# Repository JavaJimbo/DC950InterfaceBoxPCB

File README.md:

# DC950InterfaceBoxPCB
Interface box released for production in December 2017

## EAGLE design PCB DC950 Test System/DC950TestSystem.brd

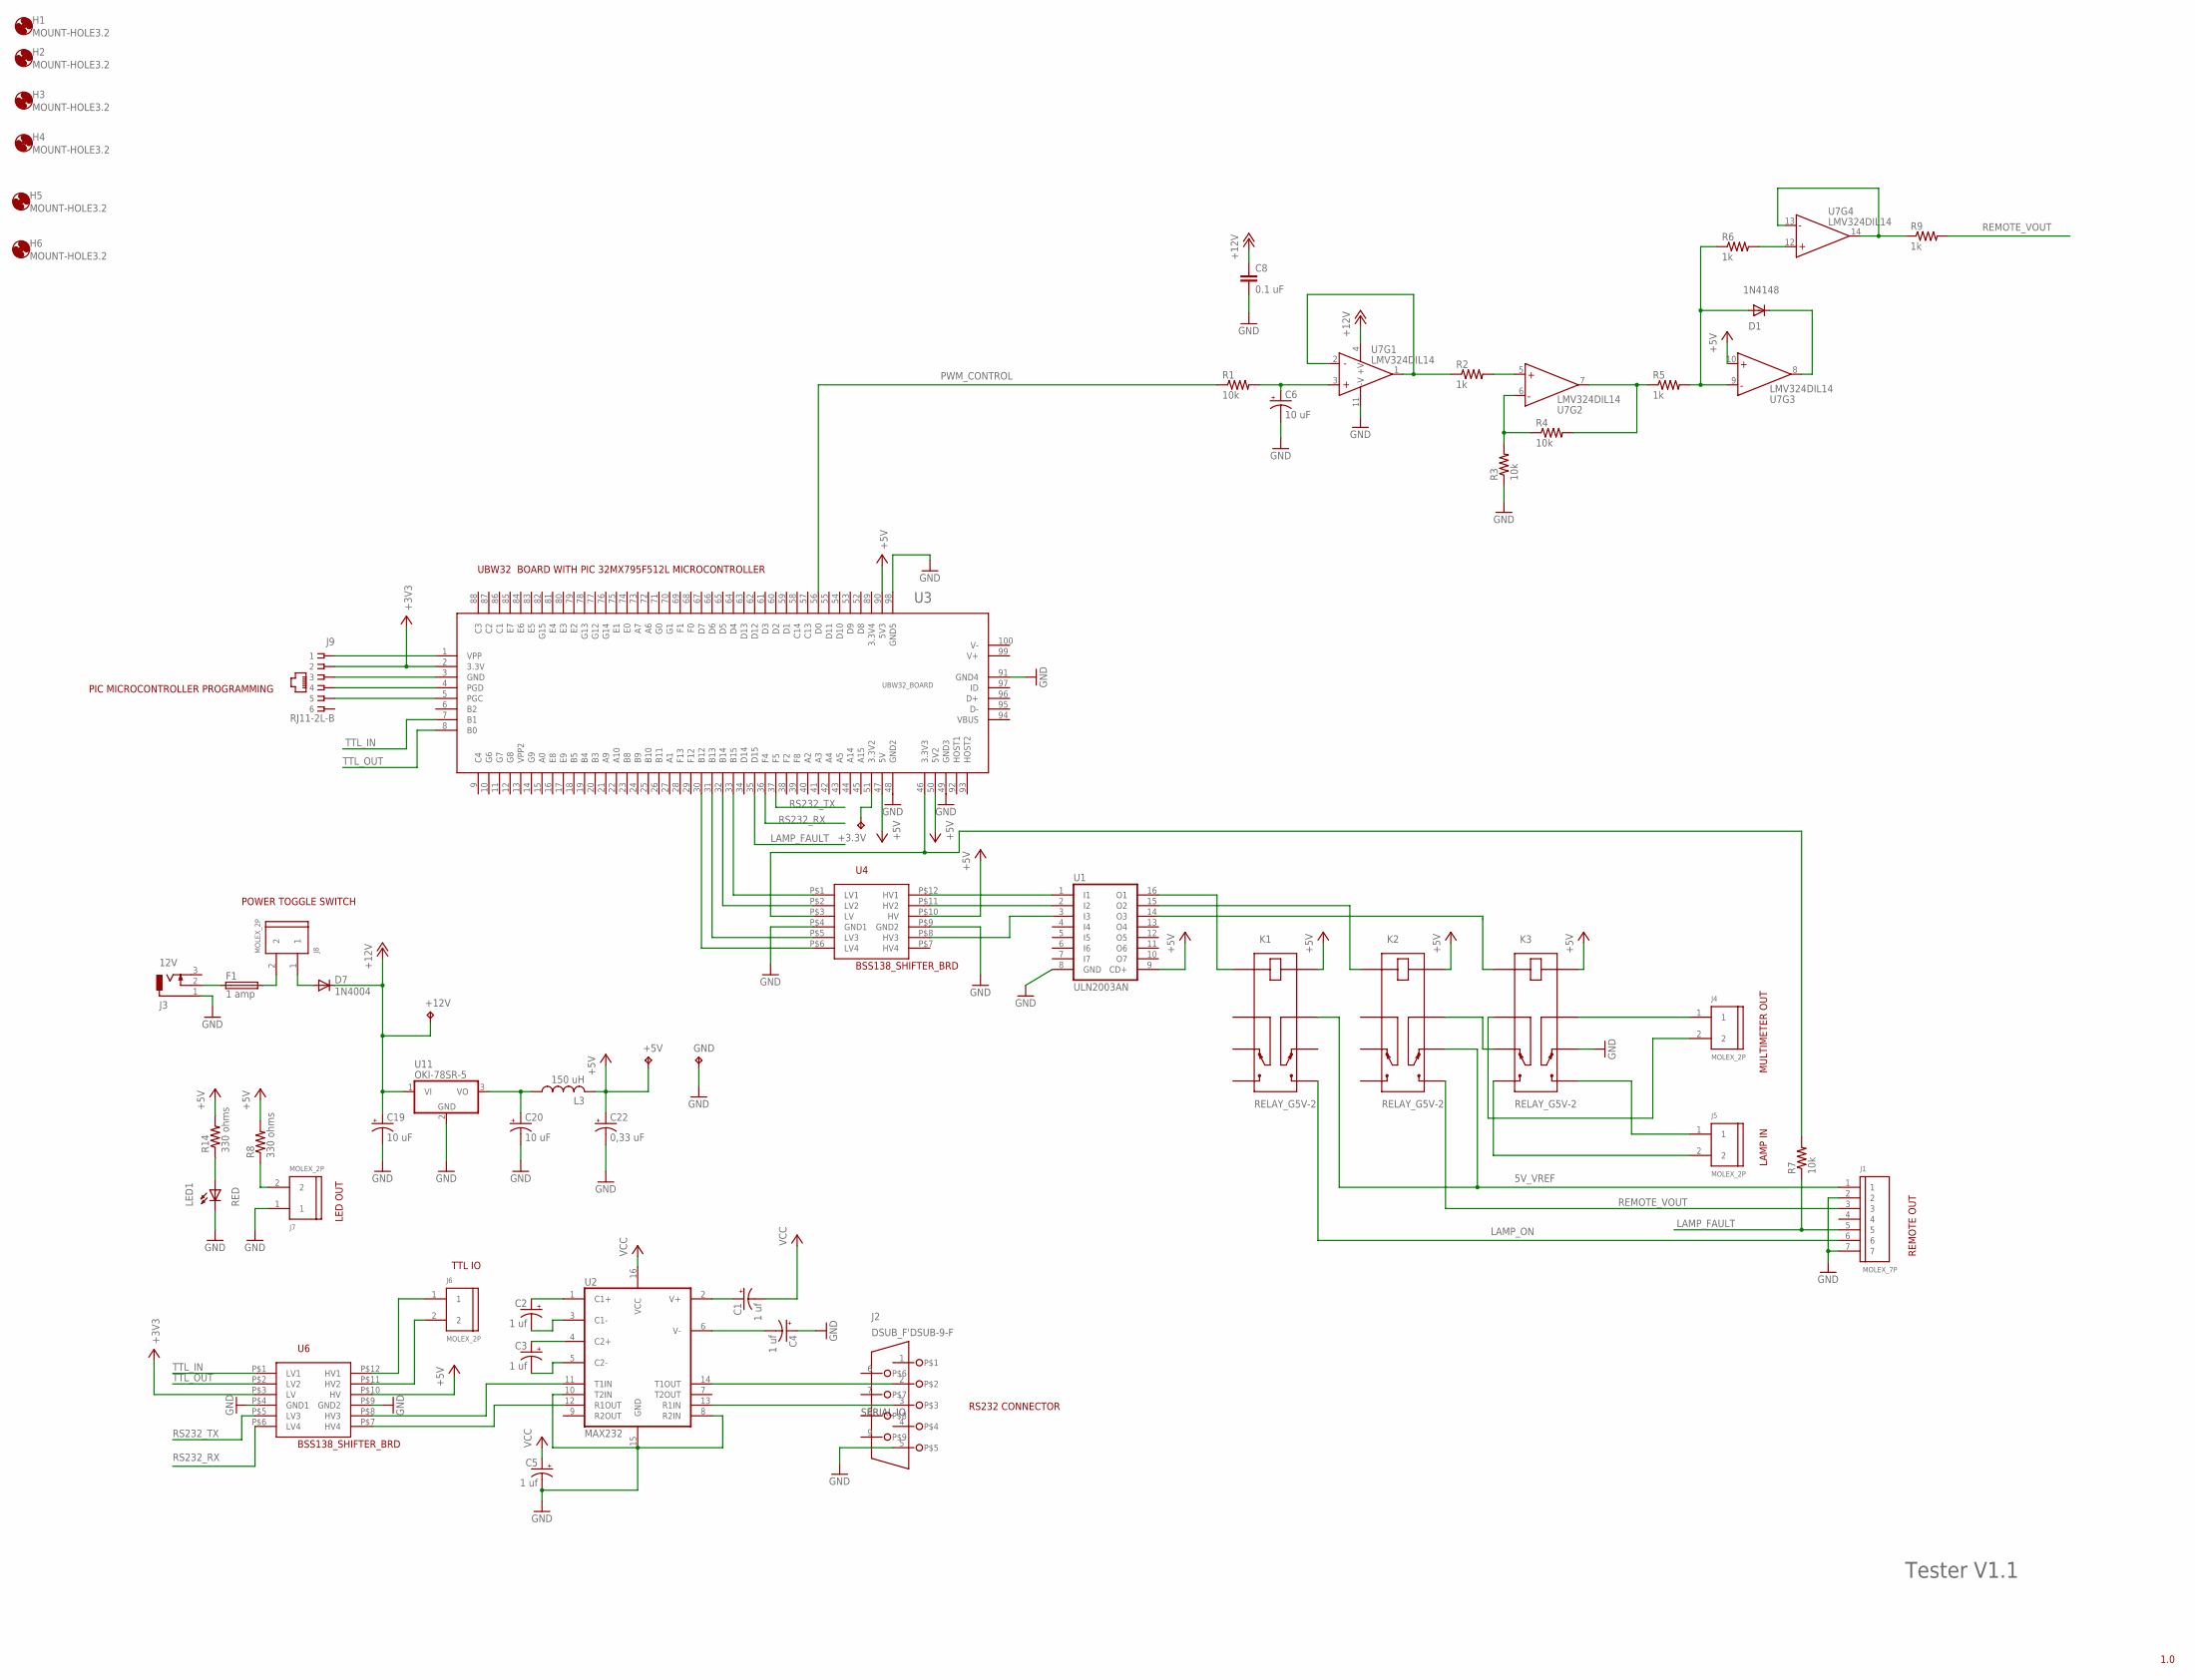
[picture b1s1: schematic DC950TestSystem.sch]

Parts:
+3.3V, +5V, +12V: TP; TESTPAD
C1, C2, C3, C4, C5: 1 uf; E2-5
C6, C19, C20: 10 uF; E2-5
C8: 0.1 uF; C5B2.5
C22: 0,33 uF; E2-5
D1: 1N4148; DO35-10
D7: 1N4004; DO41-10
F1: 1 amp; SH22,5
GND: TP; TESTPAD
H1, H2, H3, H4, H5, H6: MOUNT-HOLE3.2; 3,2
J1: MOLEX_7P
J2: DSUB_F'DSUB-9-F; H5M09RA
J3: 12V; DCJ0303
J4, J5, J6, J7, J8: MOLEX_2P
J9: RJ11-2L-B; RJ11-NO_SHIELD
K1, K2, K3: RELAY_G5V-2
L3: 150 uH; 0204/7
LED1: RED; LED5MM
R1, R3, R4, R7: 10k; 1/4_WATT
R2, R5, R6, R9: 1k; 1/4_WATT
R8, R14: 330 ohms; 0207/10
U1: ULN2003AN; DIL16
U2: MAX232; DIL16
U3: UBW32_BOARD; UBW32
U4, U6: BSS138_SHIFTER_BRD
U7: LMV324DIL14; DIL14
U11: OKI-78SR-5; TO220V

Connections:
3.3V4: U3.89 (3.3V4)
5V_VREF: J1.1, K1.13, K2.11
+3V3: J9.2, U3.2 (3.3V), U6.P$3 (LV)
+5V: +5V.P$1, C22.+, K1.16, K2.16, K3.16, L3.2, R8.2, R14.2, U1.9 (CD+), U3.47 (5V), U3.50 (5V2), U3.90 (5V3), U4.P$10 (HV), U6.P$10 (HV), U7.10 (+IN)
+12V: +12V.P$1, C8.1, C19.+, D7.C, U7.4 (+V), U11.1 (VI)
GND: C4.+, C5.-, C6.-, C8.2, C19.-, C20.-, C22.-, GND.P$1, J1.2, J1.7, J2.5, J3.1, J7.1, K3.11, LED1.K (C), R3.1, U1.8 (GND), U2.8 (R2IN), U2.10 (T2IN), U2.15 (GND), U3.48 (GND2), U3.49 (GND3), U3.91 (GND4), U3.98 (GND5), U4.P$4 (GND1), U4.P$9 (GND2), U6.P$4 (GND1), U6.P$9 (GND2), U7.11 (-V), U11.2 (GND)
LAMP_FAULT: J1.5, R7.1, U3.35 (D15)
LAMP_ON: J1.6, K1.9
unnamed: F1.1, J3.2
unnamed: J9.3, U3.3 (GND)
unnamed: F1.2, J8.2
unnamed: U2.12 (R1OUT), U6.P$7 (HV4)
unnamed: U2.11 (T1IN), U6.P$8 (HV3)
unnamed: J9.1, U3.1 (VPP)
unnamed: J6.1, U6.P$12 (HV1)
unnamed: J9.4, U3.4 (PGD)
unnamed: J9.5, U3.5 (PGC)
unnamed: R2.1, U7.1 (OUT), U7.2 (-IN)
unnamed: C6.+, R1.2, U7.3 (+IN)
unnamed: R3.2, R4.1, U7.6 (-IN)
unnamed: R4.2, R5.1, U7.7 (OUT)
unnamed: J6.2, U6.P$11 (HV2)
unnamed: R2.2, U7.5 (+IN)
unnamed: D1.A, R5.2, R6.1, U7.9 (-IN)
unnamed: D1.C, U7.8 (OUT)
unnamed: LED1.A, R14.1
unnamed: J2.2, U2.14 (T1OUT)
unnamed: J2.3, U2.13 (R1IN)
unnamed: R6.2, U7.12 (+IN)
unnamed: R7.2, U3.46 (3.3V3), U4.P$3 (LV)
unnamed: C2.+, U2.1 (C1+)
unnamed: C2.-, U2.3 (C1-)
unnamed: C3.+, U2.4 (C2+)
unnamed: C3.-, U2.5 (C2-)
unnamed: C1.+, U2.2 (V+)
unnamed: C4.-, U2.6 (V-)
unnamed: U3.33 (B15), U4.P$1 (LV1)
unnamed: U3.32 (B14), U4.P$2 (LV2)
unnamed: U3.31 (B13), U4.P$5 (LV3)
unnamed: U3.30 (B12), U4.P$6 (LV4)
unnamed: +3.3V.P$1, U3.51 (3.3V2)
unnamed: U1.1 (I1), U4.P$12 (HV1)
unnamed: U1.2 (I2), U4.P$11 (HV2)
unnamed: U1.3 (I3), U4.P$8 (HV3)
unnamed: J7.2, R8.1
unnamed: K1.1, U1.16 (O1)
unnamed: K2.1, U1.15 (O2)
unnamed: K3.1, U1.14 (O3)
unnamed: D7.A, J8.1
unnamed: C20.+, L3.1, U11.3 (VO)
unnamed: J4.1, K3.13
unnamed: J4.2, K3.4
unnamed: J5.1, K3.9
unnamed: J5.2, K3.8
unnamed: K2.13, K3.6
unnamed: R9.1, U7.13 (-IN), U7.14 (OUT)
PWM_CONTROL: R1.1, U3.56 (D0)
REMOTE_VOUT: J1.3, K2.9, R9.2
RS232_RX: U3.36 (F4), U6.P$6 (LV4)
RS232_TX: U3.37 (F5), U6.P$5 (LV3)
TTL_IN: U3.7 (B1), U6.P$1 (LV1)
TTL_OUT: U3.8 (B0), U6.P$2 (LV2)
V+: U3.99 (V+)
V-: U3.100 (V-)
VBUS: U3.94 (VBUS)
VCC: C1.-, C5.+, U2.16 (VCC)

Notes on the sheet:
SERIAL IO
1.0
Tester V1.1
MULTIMETER OUT
LAMP IN
REMOTE OUT
LED OUT
TTL IO
POWER TOGGLE SWITCH
RS232 CONNECTOR
PIC MICROCONTROLLER PROGRAMMING
UBW32 BOARD WITH PIC 32MX795F512L MICROCONTROLLER

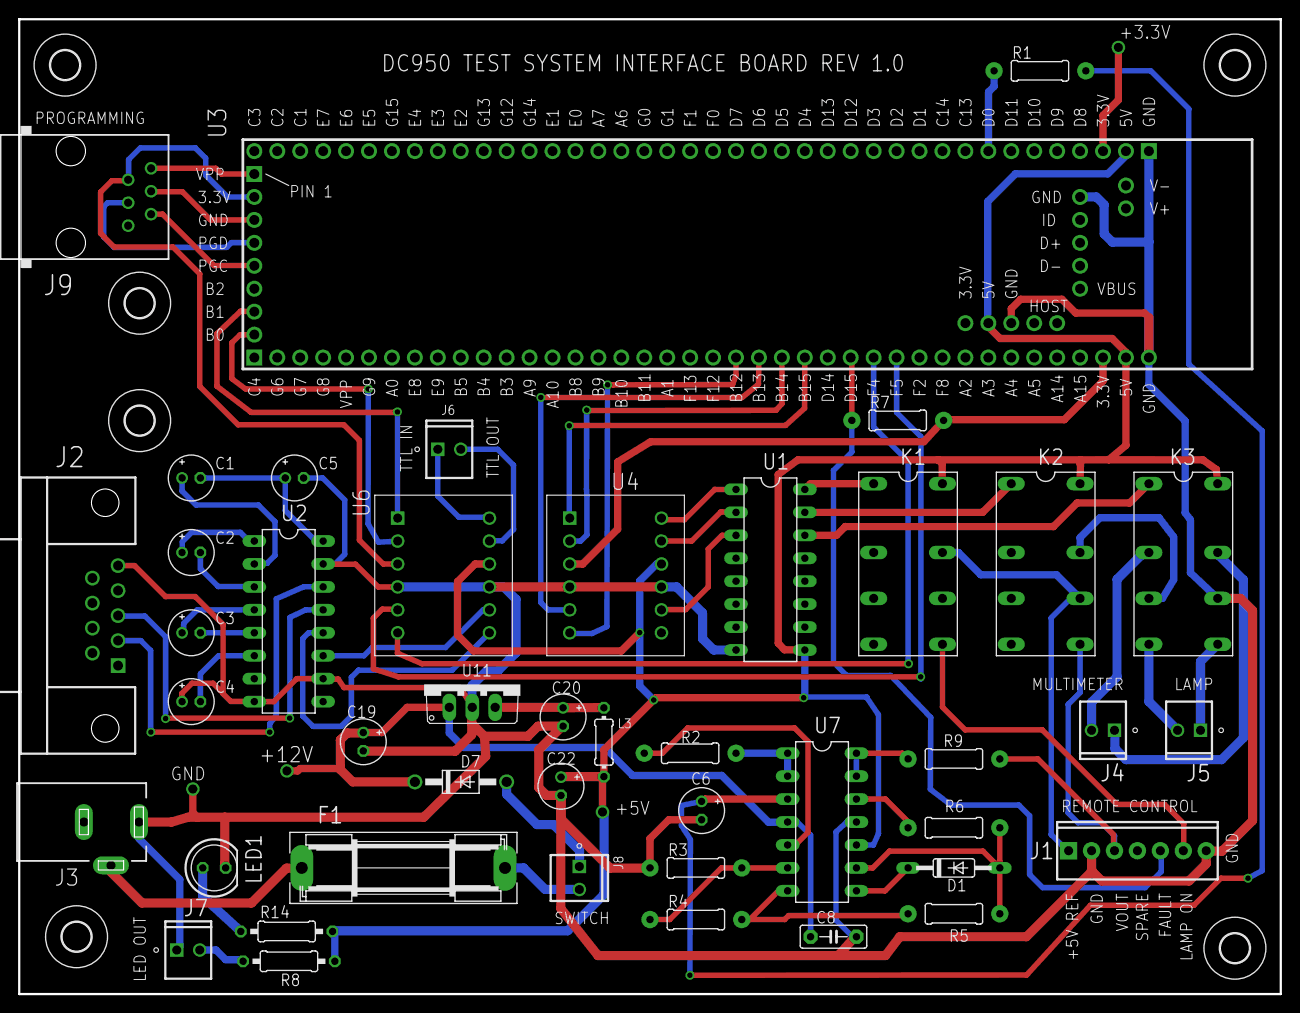
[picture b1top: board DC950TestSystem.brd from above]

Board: 2 copper layers, 139.7 x 108.0 mm, 54 parts (0 on the bottom side), 62 nets.

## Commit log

2017-12-29 Add files via upload
    First version of interface box - four boards fabricated December 2017
